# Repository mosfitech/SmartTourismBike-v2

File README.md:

smarttourismbikev2 | BIKEBIKEAJA TA EL

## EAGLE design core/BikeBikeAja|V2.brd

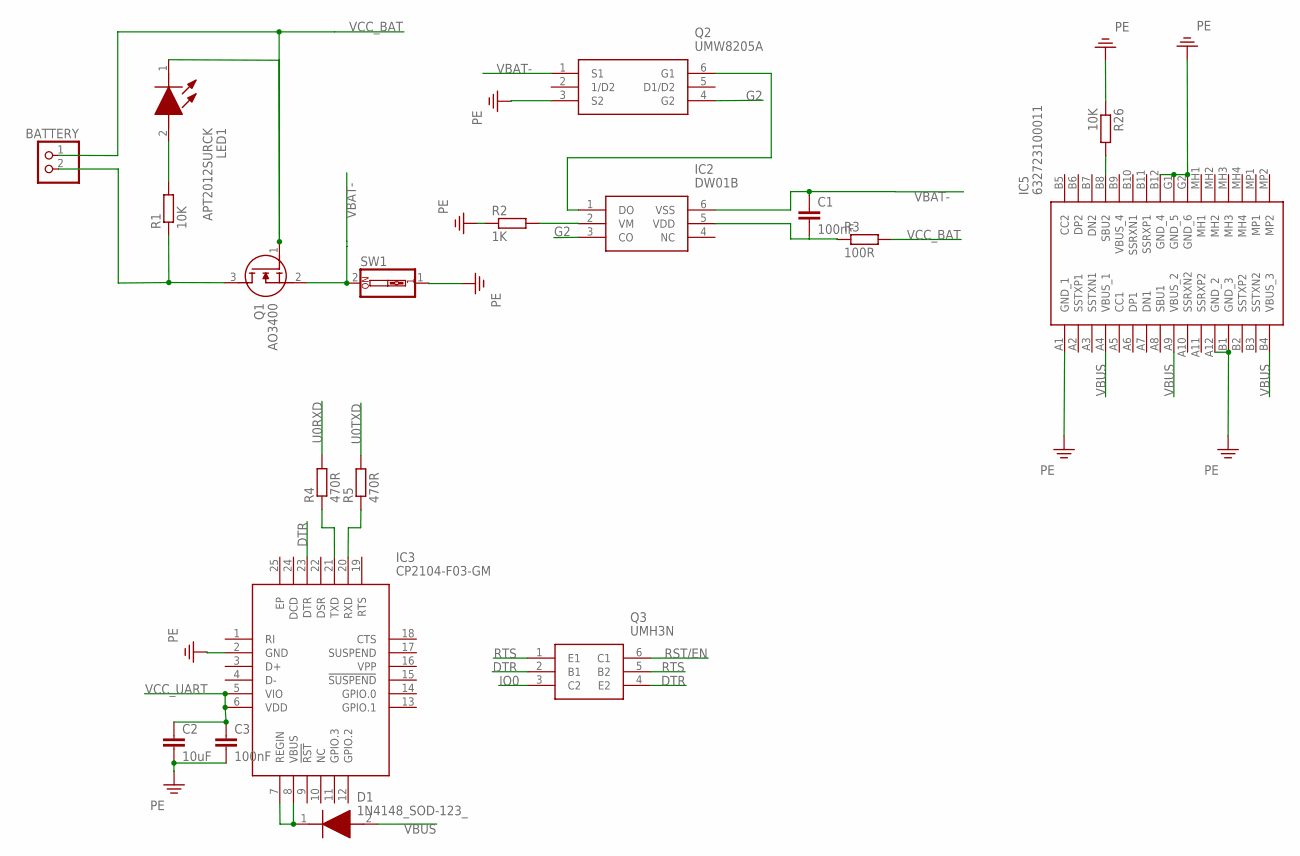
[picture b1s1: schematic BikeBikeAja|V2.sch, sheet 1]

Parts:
BATTERY: PINHD-1X2; 1X02
C1, C3: 100nF; C1206
C2: 10uF; C1206
D1: 1N4148_SOD-123_; SOD3716X135N
IC2: DW01B; SOT95P280X145-6N
IC3: CP2104-F03-GM; QFN50P400X400X80-25N
IC5: 632723100011
LED1: APT2012SURCK; LEDC2012X85N
Q1: AO3400; SOT95P280X125-3N
Q2: UMW8205A; SOT95P285X140-6N
Q3: UMH3N; SOT65P230X110-6N
R1, R26: 10K; R0805
R2: 1K; R0805
R3: 100R; R0805
R4, R5: 470R; R0805
SW1: SW_DIP-1; EDG-01

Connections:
DTR: IC3.23 (DTR), Q3.2 (B1), Q3.4 (E2)
G2: IC2.3 (CO), Q2.4 (G2)
IO0: Q3.3 (C2); also elsewhere on the board
unnamed: LED1.2 (A), R1.2
unnamed: BATTERY.1, LED1.1 (K), Q1.1 (G)
unnamed: BATTERY.2, Q1.3 (D), R1.1
unnamed: Q1.2 (S), SW1.2
unnamed: IC2.1 (DO), Q2.6 (G1)
unnamed: C1.1, IC2.6 (VSS)
unnamed: C1.2, IC2.5 (VDD), R3.1
unnamed: IC2.2 (VM), R2.2
unnamed: D1.1 (K), IC3.7 (REGIN), IC3.8 (VBUS)
unnamed: IC3.21 (TXD), R4.1
unnamed: IC3.20 (RXD), R5.1
unnamed: IC5.B8 (SBU2), R26.2
PE: C2.2, C3.2, IC3.2 (GND), IC5.A1 (GND_1), IC5.A12 (GND_2), IC5.B1 (GND_3), IC5.B12 (GND_4), IC5.G1 (GND_5), IC5.G2 (GND_6), Q2.3 (S2), R2.1, R26.1, SW1.1; also elsewhere on the board
RST/EN: Q3.6 (C1); also elsewhere on the board
RTS: Q3.1 (E1), Q3.5 (B2)
U0RXD: R4.2; also elsewhere on the board
U0TXD: R5.2; also elsewhere on the board
VBAT-: Q2.1 (S1)
VBUS: D1.2 (A), IC5.A4 (VBUS_1), IC5.A9 (VBUS_2), IC5.B4 (VBUS_3); also elsewhere on the board
VCC_BAT: R3.2
VCC_UART: C2.1, C3.1, IC3.5 (VIO), IC3.6 (VDD)

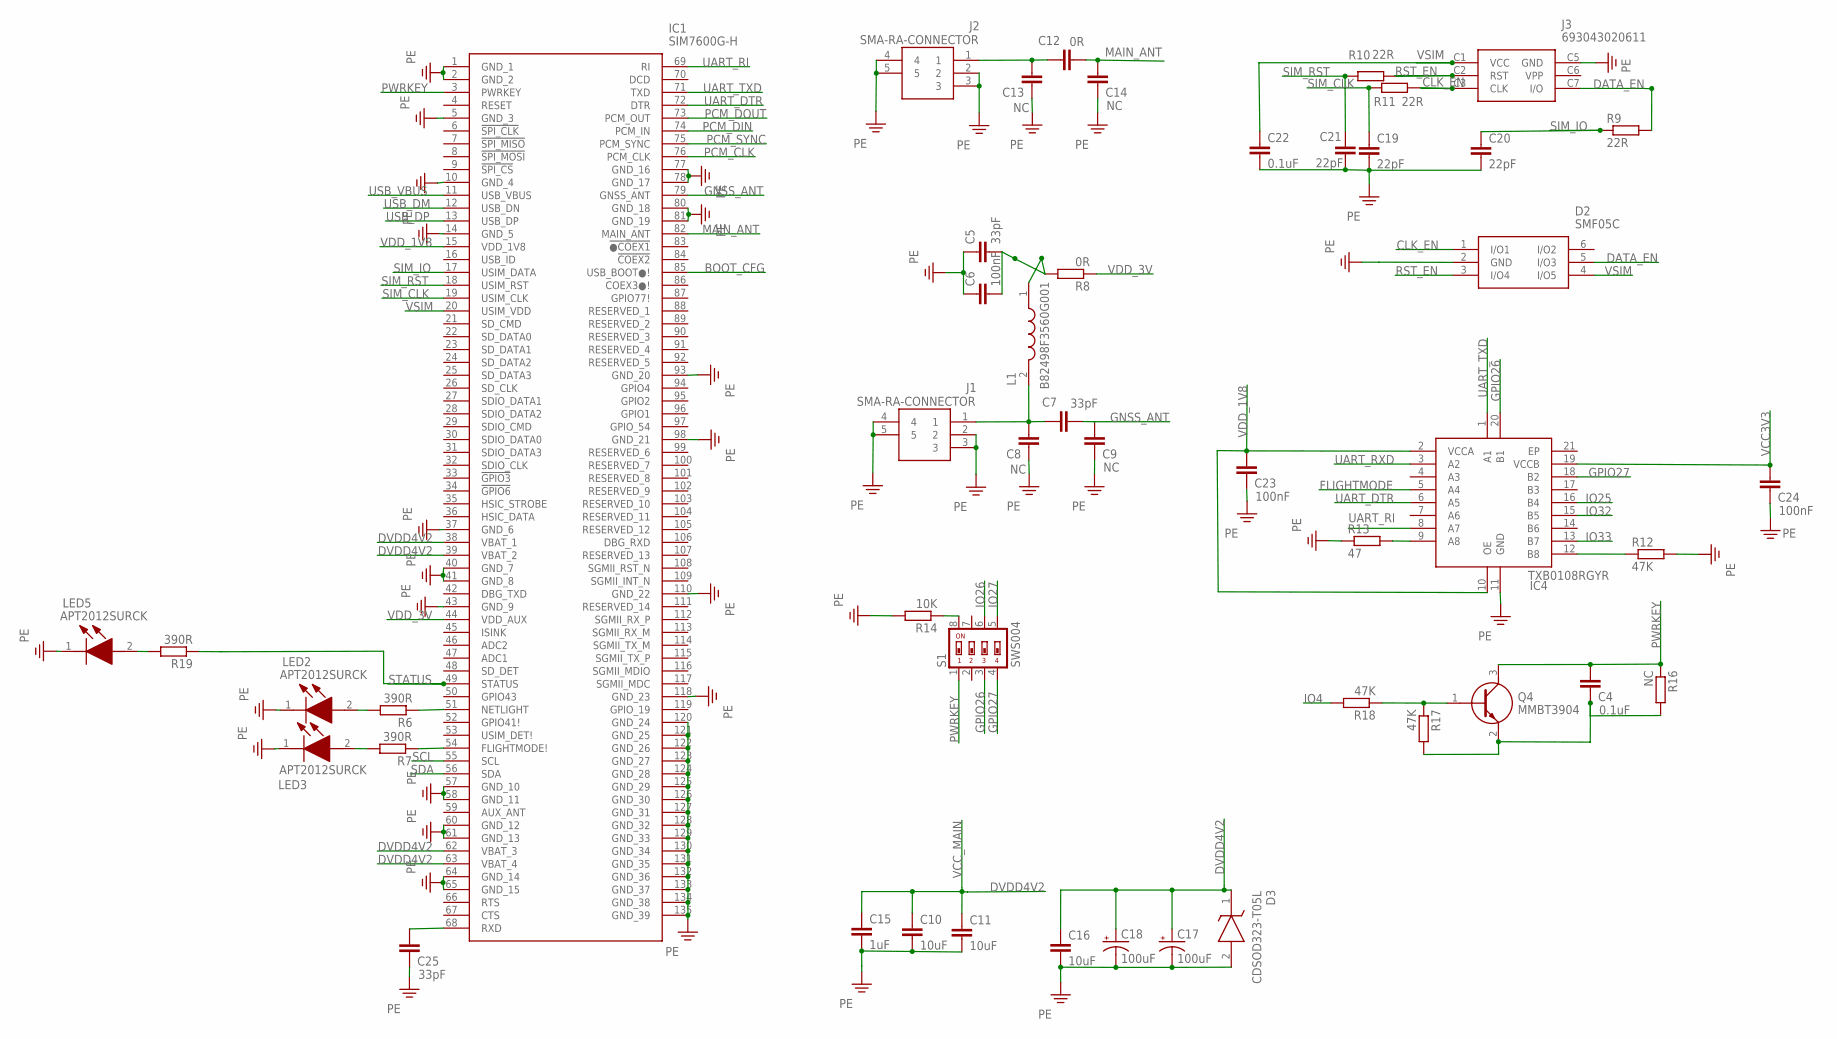
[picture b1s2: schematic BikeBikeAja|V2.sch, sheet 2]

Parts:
C4, C22: 0.1uF; C1206
C5, C7, C25: 33pF; C1206
C6, C23, C24: 100nF; C1206
C8, C9, C13, C14: NC; C1206
C10, C11, C16: 10uF; C1206
C12: 0R; C1206
C15: 1uF; C1206
C17, C18: 100uF; A/3216-18W
C19, C20, C21: 22pF; C1206
D2: SMF05C; SOT65P210X110-6N
D3: CDSOD323-T05L; SOD2513X114N
IC1: SIM7600G-H; SIM7600GH
IC4: TXB0108RGYR; SN74LVC541ARGYR
J1, J2: SMA-RA-CONNECTOR; SMARACONNECTOR
J3: 693043020611
L1: B82498F3560G001; B82498F
LED2, LED3, LED5: APT2012SURCK; LEDC2012X85N
Q4: MMBT3904; SOT95P240X120-3N
R6, R7, R19: 390R; R0805
R8: 0R; R0805
R9, R10, R11: 22R; R0805
R12, R17, R18: 47K; R0805
R13: 47; R0805
R14: 10K; R0805
R16: NC; R0805
S1: SWS004; SMS-004

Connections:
BOOT_CFG: IC1.85 (USB_BOOT●!)
CLK_EN: D2.1 (I/O1), J3.C3 (CLK), R11.1
DATA_EN: D2.5 (I/O3), J3.C7 (I/O)
DVDD4V2: IC1.38 (VBAT_1), IC1.39 (VBAT_2), IC1.62 (VBAT_3), IC1.63 (VBAT_4); also elsewhere on the board
FLIGHTMODE: IC4.5 (A4)
GNSS_ANT: IC1.79 (GNSS_ANT)
GPIO26: IC4.20 (B1), S1.3
GPIO27: IC4.18 (B2), S1.4
IO4: R18.2; also elsewhere on the board
IO25: IC4.16 (B4); also elsewhere on the board
IO26: S1.6; also elsewhere on the board
IO27: S1.5; also elsewhere on the board
IO32: IC4.15 (B5); also elsewhere on the board
IO33: IC4.13 (B7); also elsewhere on the board
MAIN_ANT: C12.2, C14.2, IC1.82 (MAIN_ANT)
unnamed: IC1.51 (NETLIGHT), R6.1
unnamed: LED2.2 (A), R6.2
unnamed: LED3.2 (A), R7.2
unnamed: IC1.54 (FLIGHTMODE!), R7.1
unnamed: C5.1, C6.1
unnamed: C5.2, C6.2, L1.1, R8.2
unnamed: C7.1, C8.2, J1.1, L1.2
unnamed: C7.2, C9.2
unnamed: C10.1, C11.1, C15.1
unnamed: C16.1, C17.+, C18.+, D3.1 (K)
unnamed: C12.1, C13.2, J2.1
unnamed: IC4.12 (B8), R12.1
unnamed: IC4.9 (A8), R13.2
unnamed: R14.1, S1.8
unnamed: C25.2, IC1.68 (RXD)
unnamed: Q4.1 (B), R17.1, R18.1
unnamed: C4.1, Q4.2 (E), R16.2, R17.2
unnamed: LED5.2 (A), R19.2
PCM_CLK: IC1.76 (PCM_CLK)
PCM_DIN: IC1.74 (PCM_IN)
PCM_DOUT: IC1.73 (PCM_OUT)
PCM_SYNC: IC1.75 (PCM_SYNC)
PE: C8.1, C9.1, C10.2, C11.2, C13.1, C14.1, C15.2, C16.2, C17.-, C18.-, C19.2, C20.2, C21.2, C22.2, C23.1, C24.1, C25.1, D2.2 (GND), D3.2 (A), IC1.1 (GND_1), IC1.2 (GND_2), IC1.5 (GND_3), IC1.10 (GND_4), IC1.14 (GND_5), IC1.37 (GND_6), IC1.40 (GND_7), IC1.41 (GND_8), IC1.43 (GND_9), IC1.57 (GND_10), IC1.58 (GND_11), IC1.60 (GND_12), IC1.61 (GND_13), IC1.64 (GND_14), IC1.65 (GND_15), IC1.77 (GND_16), IC1.78 (GND_17), IC1.80 (GND_18), IC1.81 (GND_19), IC1.93 (GND_20), IC1.98 (GND_21), IC1.110 (GND_22), IC1.118 (GND_23), IC1.120 (GND_24), IC1.121 (GND_25), IC1.122 (GND_26), IC1.123 (GND_27), IC1.124 (GND_28), IC1.125 (GND_29), IC1.126 (GND_30), IC1.127 (GND_31), IC1.128 (GND_32), IC1.129 (GND_33), IC1.130 (GND_34), IC1.131 (GND_35), IC1.132 (GND_36), IC1.133 (GND_37), IC1.134 (GND_38), IC1.135 (GND_39), IC4.11 (GND), J1.2, J1.3, J1.4, J1.5, J2.2, J2.3, J2.4, J2.5, J3.C5 (GND), LED2.1 (K), LED3.1 (K), LED5.1 (K), R12.2, R13.1, R14.2; also elsewhere on the board
PWRKEY: C4.2, IC1.3 (PWRKEY), Q4.3 (C), R16.1, S1.1
RST_EN: D2.3 (I/O4), J3.C2 (RST), R10.1
SCL: IC1.55 (SCL)
SDA: IC1.56 (SDA)
SIM_CLK: C19.1, IC1.19 (USIM_CLK), R11.2
SIM_IO: C20.1, IC1.17 (USIM_DATA), R9.1
SIM_RST: C21.1, IC1.18 (USIM_RST), R10.2
STATUS: IC1.49 (STATUS), R19.1
UART_DTR: IC1.72 (DTR), IC4.6 (A5)
UART_RI: IC1.69 (RI), IC4.8 (A7)
UART_RXD: IC4.3 (A2)
UART_TXD: IC1.71 (TXD), IC4.1 (A1)
USB_DM: IC1.12 (USB_DN)
USB_DP: IC1.13 (USB_DP)
USB_VBUS: IC1.11 (USB_VBUS)
VCC3V3: C24.2, IC4.19 (VCCB); also elsewhere on the board
VDD_1V8: C23.2, IC1.15 (VDD_1V8), IC4.2 (VCCA), IC4.10 (OE)
VDD_3V: IC1.44 (VDD_AUX), R8.1
VSIM: C22.1, D2.4 (I/O5), IC1.20 (USIM_VDD), J3.C1 (VCC)

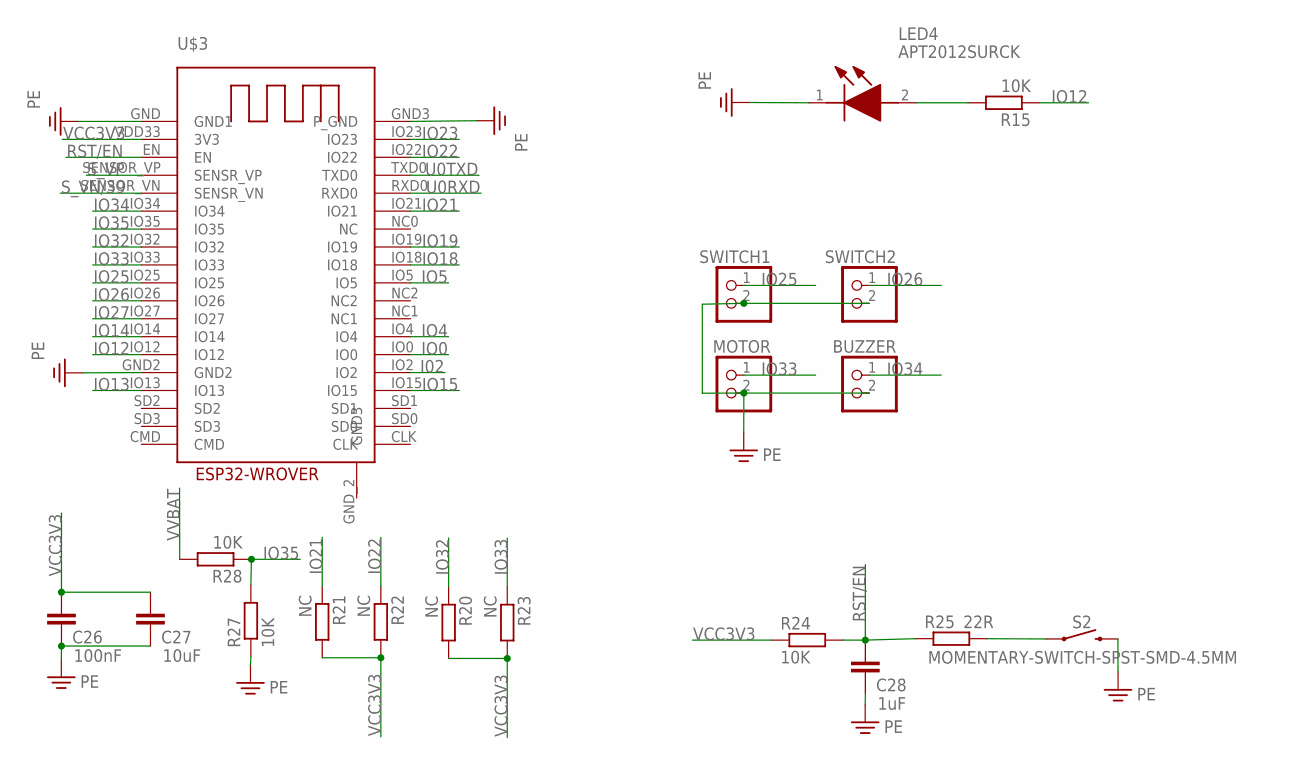
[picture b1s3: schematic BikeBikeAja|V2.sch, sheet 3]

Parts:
BUZZER: PINHD-1X2; 1X02
C26: 100nF; C1206
C27: 10uF; C1206
C28: 1uF; C1206
LED4: APT2012SURCK; LEDC2012X85N
MOTOR: PINHD-1X2; 1X02
R15, R24, R27, R28: 10K; R0805
R20, R21, R22, R23: NC; R0805
R25: 22R; R0805
S2: MOMENTARY-SWITCH-SPST-SMD-4.5MM; TACTILE_SWITCH_SMD_4.5MM
SWITCH1, SWITCH2: PINHD-1X2; 1X02
U$3: ESP32-WROVER

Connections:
I02: U$3.IO2
IO0: U$3.IO0; also elsewhere on the board
IO4: U$3.IO4; also elsewhere on the board
IO5: U$3.IO5
IO12: R15.1, U$3.IO12
IO13: U$3.IO13
IO14: U$3.IO14
IO15: U$3.IO15
IO18: U$3.IO18
IO19: U$3.IO19
IO21: R21.1, U$3.IO21
IO22: R22.1, U$3.IO22
IO23: U$3.IO23
IO25: SWITCH1.1, U$3.IO25; also elsewhere on the board
IO26: SWITCH2.1, U$3.IO26; also elsewhere on the board
IO27: U$3.IO27; also elsewhere on the board
IO32: R20.1, U$3.IO32; also elsewhere on the board
IO33: MOTOR.1, R23.1, U$3.IO33; also elsewhere on the board
IO34: BUZZER.1, U$3.IO34
IO35: R27.2, R28.1, U$3.IO35
unnamed: R25.2, S2.2 (1), S2.3 (1)
unnamed: LED4.2 (A), R15.2
PE: BUZZER.2, C26.1, C27.1, C28.1, LED4.1 (K), MOTOR.2, R27.1, S2.1 (2), S2.4 (2), SWITCH1.2, SWITCH2.2, U$3.GND (GND1), U$3.GND2, U$3.GND3 (P_GND); also elsewhere on the board
RST/EN: C28.2, R24.2, R25.1, U$3.EN; also elsewhere on the board
S_VN/39: U$3.SENSOR_VN (SENSR_VN)
S_VP: U$3.SENSOR_VP (SENSR_VP)
U0RXD: U$3.RXD0; also elsewhere on the board
U0TXD: U$3.TXD0; also elsewhere on the board
VCC3V3: C26.2, C27.2, R20.2, R21.2, R22.2, R23.2, R24.1, U$3.VDD33 (3V3); also elsewhere on the board
VVBAT: R28.2; also elsewhere on the board

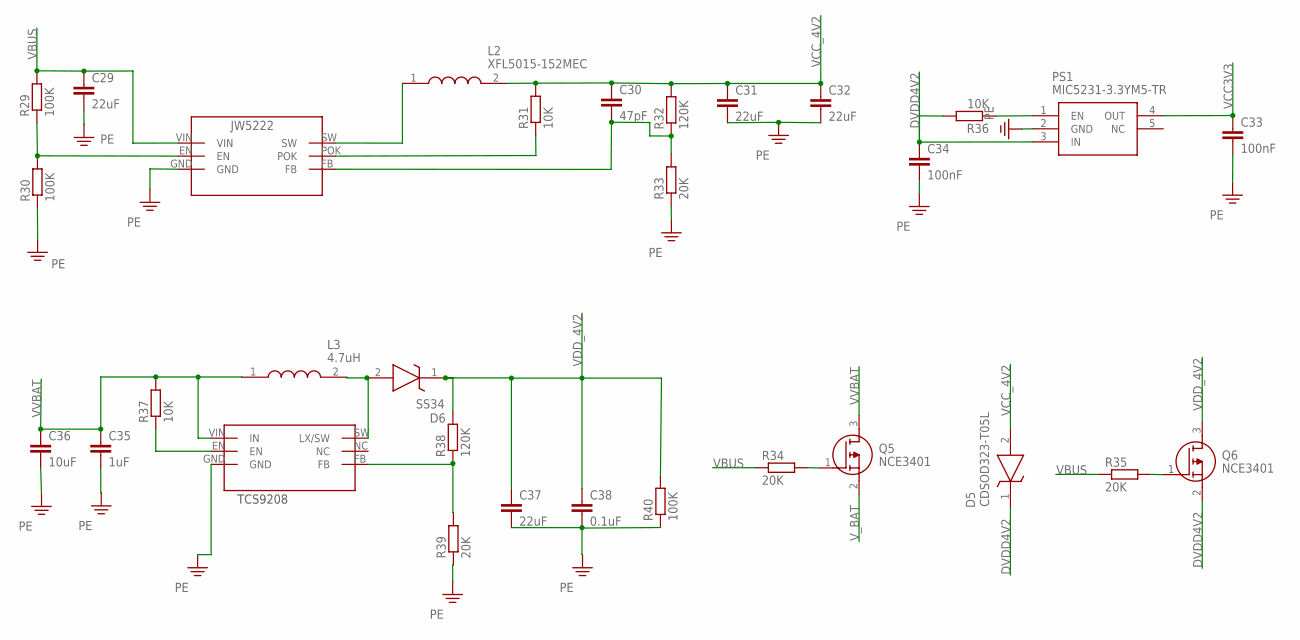
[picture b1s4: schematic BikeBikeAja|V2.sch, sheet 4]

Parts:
C29, C31, C32, C37: 22uF; C1206
C30: 47pF; C1206
C33, C34: 100nF; C1206
C35: 1uF; C1206
C36: 10uF; C1206
C38: 0.1uF; C1206
D5: CDSOD323-T05L; SOD2513X114N
D6: SS34; SOD2513X114N
L2: XFL5015-152MEC; XFL5015152MEC
L3: 4.7uH; XFL5015152MEC
PS1: MIC5231-3.3YM5-TR; SOT95P280X145-5N
Q5, Q6: NCE3401; SOT95P240X115-3N
R29, R30, R40: 100K; R0805
R31, R36, R37: 10K; R0805
R32, R38: 120K; R0805
R33, R34, R35, R39: 20K; R0805
U$1: JW5222
U$4: TCS9208

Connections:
DVDD4V2: C34.1, D5.1 (K), PS1.3 (IN), Q6.2 (S), R36.2; also elsewhere on the board
unnamed: R29.1, R30.2, U$1.EN
unnamed: L2.1, U$1.SW
unnamed: R31.1, U$1.POK
unnamed: Q5.1 (G), R34.2
unnamed: C30.2, R32.1, R33.2, U$1.FB
unnamed: Q6.1 (G), R35.2
unnamed: PS1.1 (EN), R36.1
unnamed: D6.2 (A), L3.2, U$4.SW (LX/SW)
unnamed: R37.1, U$4.EN
unnamed: R38.1, R39.2, U$4.FB
PE: C29.2, C31.2, C32.2, C33.2, C34.2, C35.2, C36.2, C37.2, C38.2, PS1.2 (GND), R30.1, R33.1, R39.1, R40.1, U$1.GND, U$4.GND; also elsewhere on the board
VBUS: C29.1, R29.2, R34.1, R35.1, U$1.VIN; also elsewhere on the board
VCC3V3: C33.1, PS1.4 (OUT); also elsewhere on the board
VCC_4V2: C30.1, C31.1, C32.1, D5.2 (A), L2.2, R31.2, R32.2
VDD_4V2: C37.1, C38.1, D6.1 (K), Q6.3 (D), R38.2, R40.2
VVBAT: C35.1, C36.1, L3.1, Q5.3 (D), R37.2; also elsewhere on the board
V_BAT: Q5.2 (S)

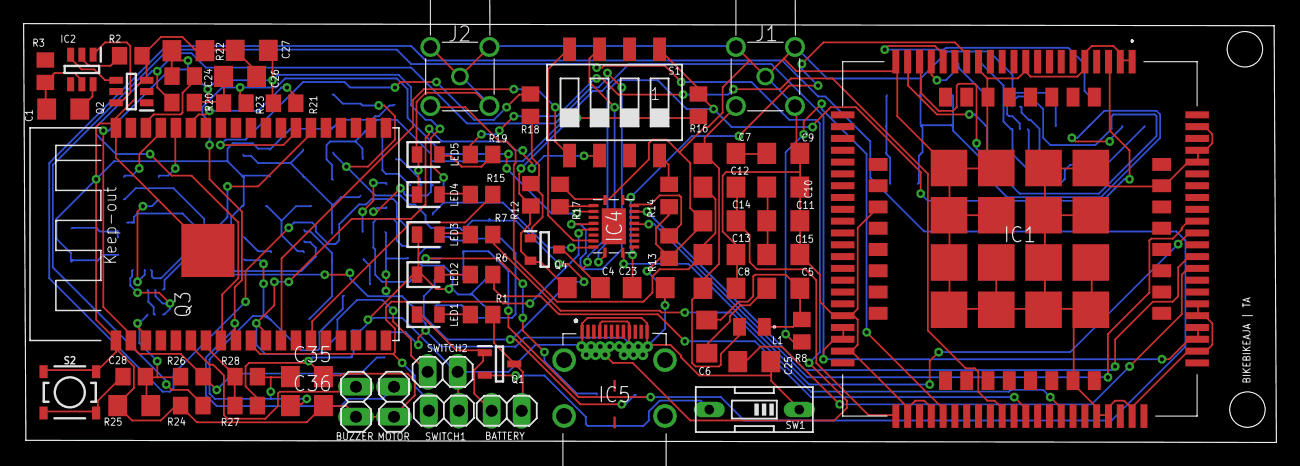
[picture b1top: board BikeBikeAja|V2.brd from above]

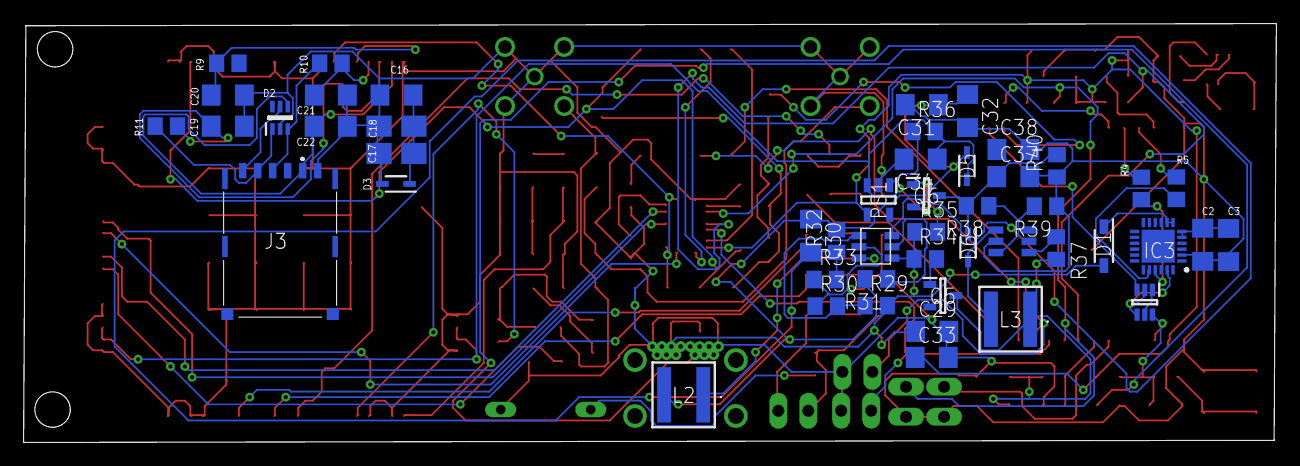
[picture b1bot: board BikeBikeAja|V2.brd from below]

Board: 2 copper layers, 106.0 x 35.5 mm, 117 parts (49 on the bottom side), 85 nets.

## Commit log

2022-11-01 first setup
2023-05-09 update code

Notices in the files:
parts and their libraries:
SparkFun-Switches: Licensing: Creative Commons ShareAlike 4.0 International - https://creativecommons.org/licenses/by-sa/4.0
